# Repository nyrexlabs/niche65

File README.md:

# niche65

The niche65 is an open source proof of concept for a split, staggered, true-wireless Bluetooth 65% mechanical keyboard. Powered by ZMK.

## No support

This project is no longer supported. All development efforts are going towards a V2.

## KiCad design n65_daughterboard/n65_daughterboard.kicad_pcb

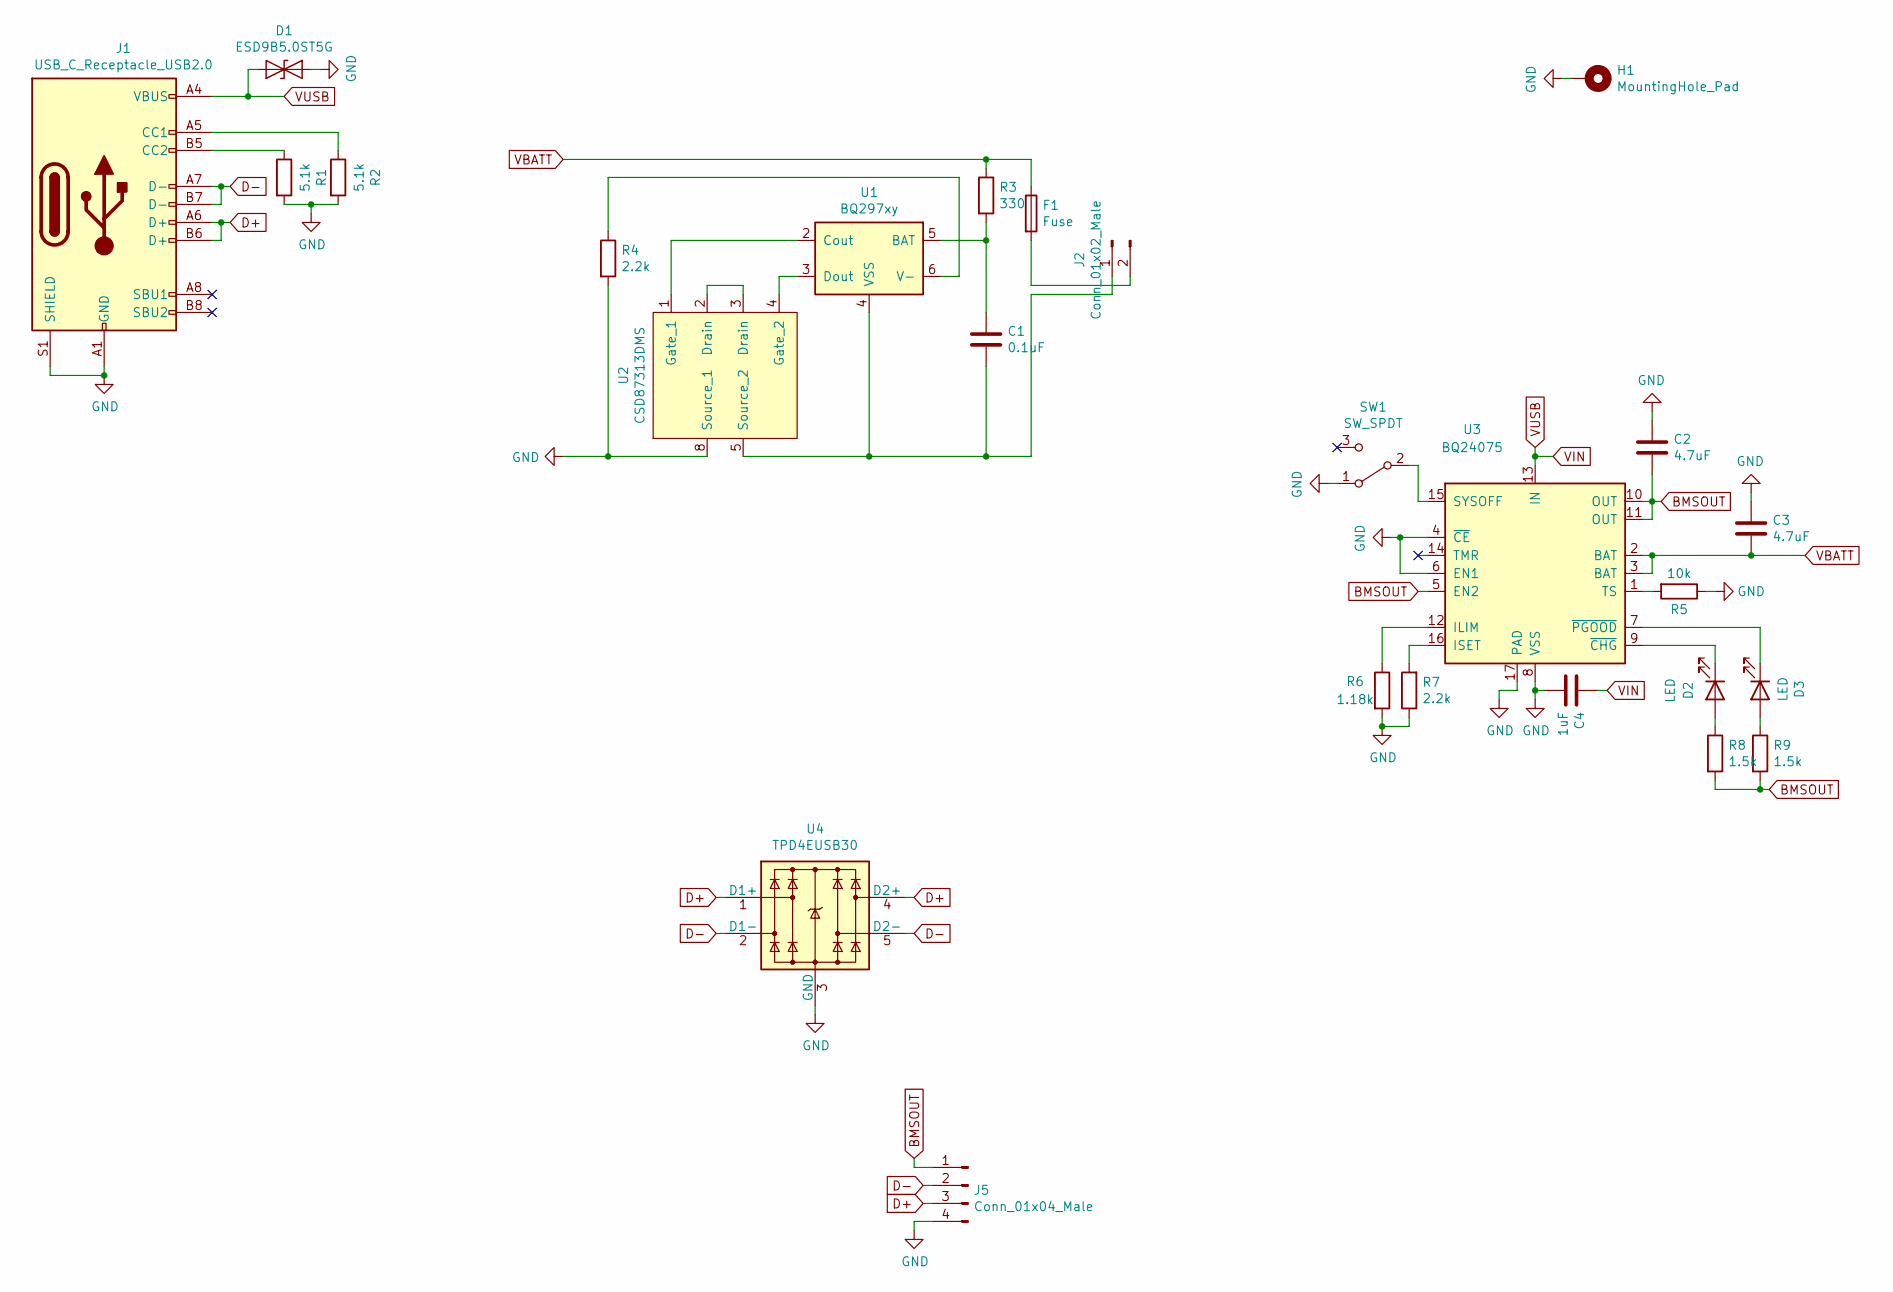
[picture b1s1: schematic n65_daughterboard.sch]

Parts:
C1: 0.1uF; C_0201_0603Metric
C2, C3: 4.7uF; C_0402_1005Metric
C4: 1uF; C_0201_0603Metric
D1: ESD9B5.0ST5G; D_0402_1005Metric
D2, D3: LED; LED_0603_1608Metric
F1: Fuse; Fuse_1206_3216Metric
H1: MountingHole_Pad; Screw Ground Pad 2mmID 5mmOD
J1: USB_C_Receptacle_USB2.0; GCT_USB4145_03_0170_C
J2: Conn_01x02_Male; JST_PH_S2B-PH-SM4-TB_1x02-1MP_P2.00mm_Horizontal
J5: Conn_01x04_Male; Molex_Pico-EZmate_78171-0004_1x04-1MP_P1.20mm_Vertical
R1, R2: 5.1k; R_0603_1608Metric
R3: 330; R_0603_1608Metric
R4, R7: 2.2k; R_0603_1608Metric
R5: 10k; R_0603_1608Metric
R6: 1.18k; R_0603_1608Metric
R8, R9: 1.5k; R_0603_1608Metric
SW1: SW_SPDT; SW_SPDTx01_Toggle_8.13x5.08mm_W7.62mm_P2.54mm
U1: BQ297xy; WSON-6_1.5x1.5mm_P0.5mm
U2: CSD87313DMS; VSON-8_3.3x3.3mm_P0.65mm_NexFET_NOTSTUPID
U3: BQ24075; VQFN-16-1EP_3x3mm_P0.5mm_EP1.68x1.68mm_ThermalVias
U4: TPD4EUSB30; USON-10_2.5x1.0mm_P0.5mm

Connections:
BMSOUT: C2.2, J5.1, R8.2, R9.2, U3.5 (EN2), U3.10 (OUT), U3.11 (OUT)
D+: J1.A6 (D+), J1.B6 (D+), J5.3, U4.1 (D1+), U4.4 (D2+)
D-: J1.A7 (D-), J1.B7 (D-), J5.2, U4.2 (D1-), U4.5 (D2-)
GND: C2.1, C3.1, C4.2, D1.2 (A2), H1.1, J1.A1 (GND), J1.A12 (GND), J1.B1 (GND), J1.B12 (GND), J1.S1 (SHIELD), J5.4, R1.2, R2.2, R4.2, R5.1, R6.2, R7.1, SW1.1 (A), U2.8 (Source_1), U3.4 (~CE), U3.6 (EN1), U3.8 (VSS), U3.17 (PAD), U4.3 (GND), U4.8 (GND); also elsewhere on the board
unnamed: C1.1, R3.2, U1.5 (BAT)
unnamed: C1.2, J2.1, U1.4 (VSS), U2.5 (Source_2)
unnamed: D2.1 (K), U3.9 (~CHG)
unnamed: D2.2 (A), R8.1
unnamed: D3.1 (K), U3.7 (~PGOOD)
unnamed: D3.2 (A), R9.1
unnamed: F1.2, J2.2
unnamed: J1.A5 (CC1), R2.1
unnamed: J1.B5 (CC2), R1.1
unnamed: R4.1, U1.6 (V-)
unnamed: R5.2, U3.1 (TS)
unnamed: R6.1, U3.12 (ILIM)
unnamed: R7.2, U3.16 (ISET)
unnamed: SW1.2 (B), U3.15 (SYSOFF)
unnamed: U1.2 (Cout), U2.1 (Gate_1)
unnamed: U1.3 (Dout), U2.4 (Gate_2)
unnamed: U2.2 (Drain), U2.3 (Drain)
VBATT: C3.2, F1.1, R3.1, U3.2 (BAT), U3.3 (BAT)
VIN: C4.1, D1.1 (A1), J1.A4 (VBUS), J1.A9 (VBUS), J1.B4 (VBUS), J1.B9 (VBUS), U3.13 (IN)

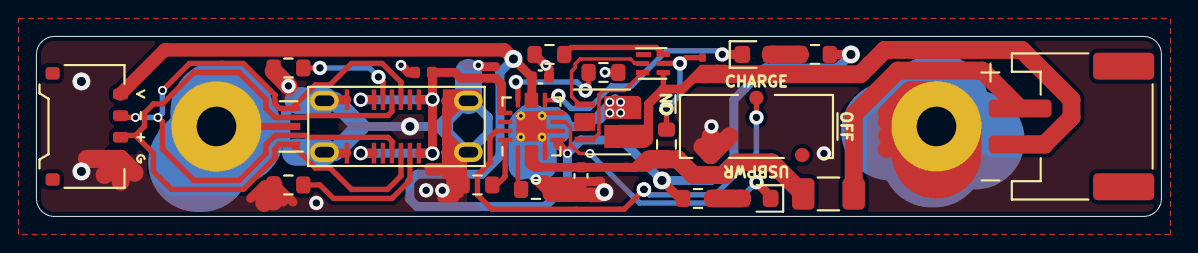
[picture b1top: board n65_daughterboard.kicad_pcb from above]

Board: 2 copper layers, 62.5 x 10.0 mm, 27 parts (0 on the bottom side), 23 nets.

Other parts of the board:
H1#2: MountingHole_Pad; Screw Ground Pad 2mmID 5mmOD

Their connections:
GND: H1#2.1; also elsewhere on the board

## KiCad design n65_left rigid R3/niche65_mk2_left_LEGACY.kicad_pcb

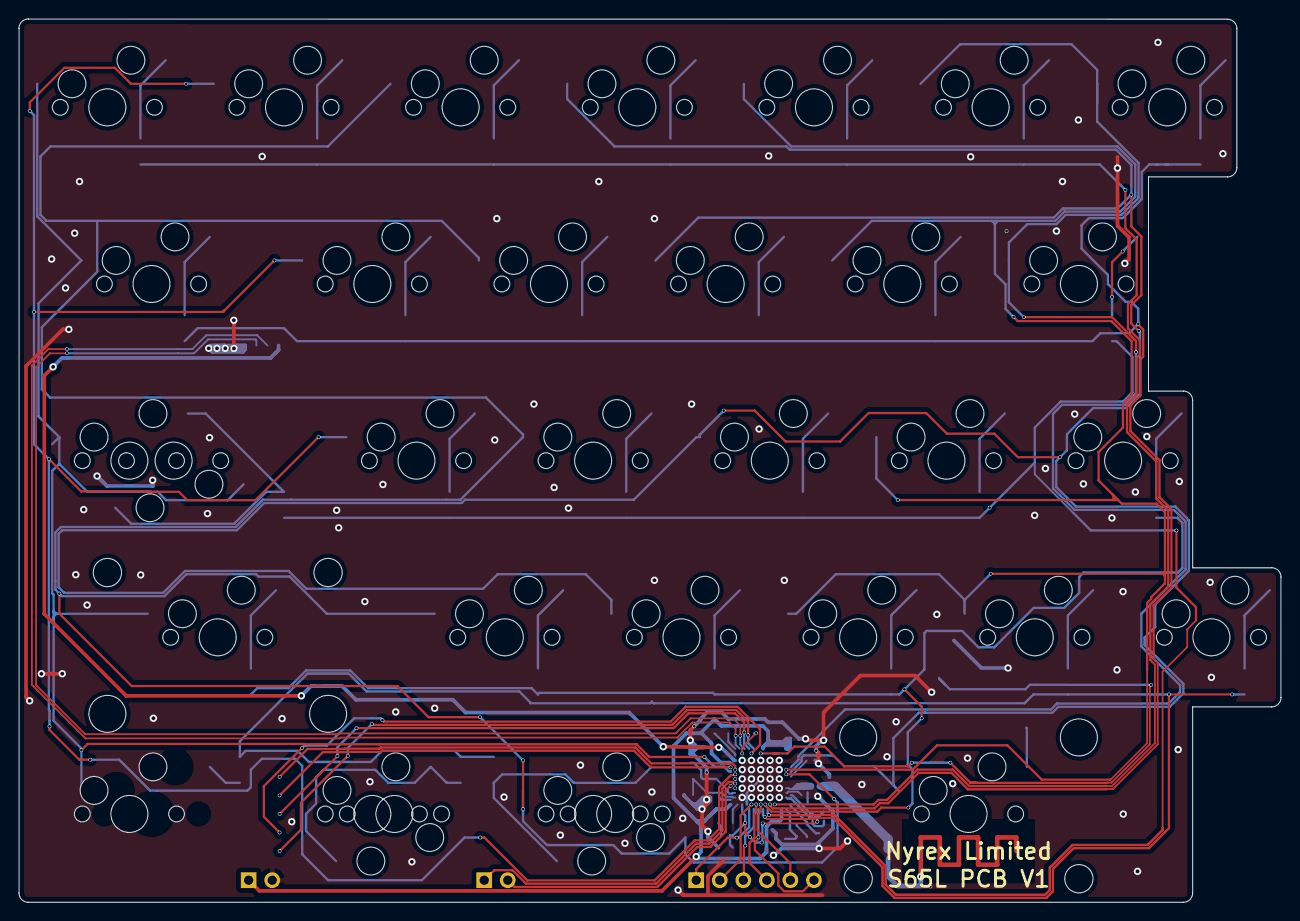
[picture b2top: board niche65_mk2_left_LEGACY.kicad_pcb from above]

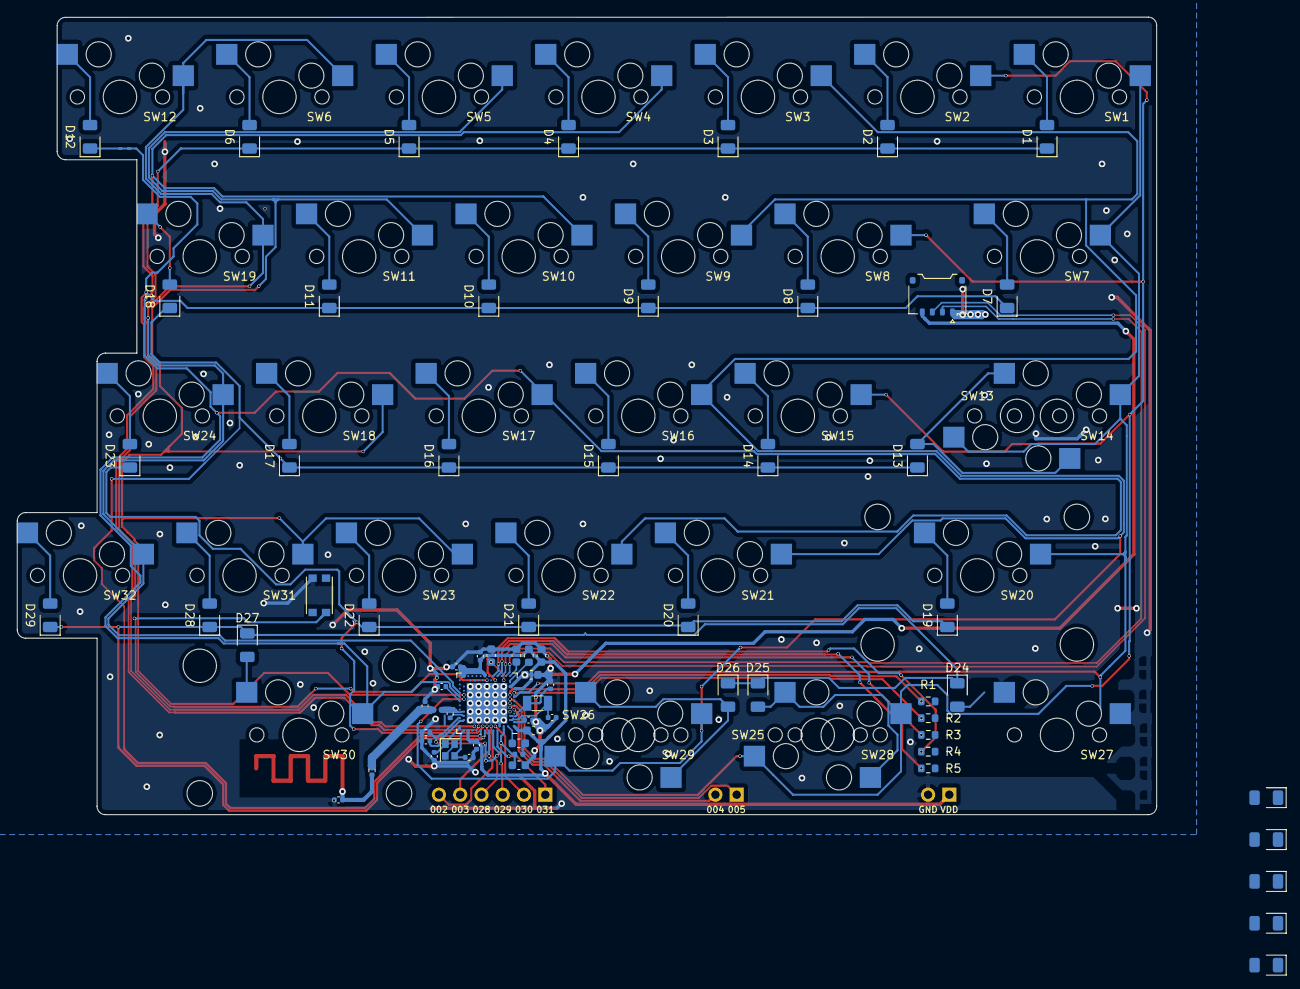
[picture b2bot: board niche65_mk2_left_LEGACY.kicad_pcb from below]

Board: 2 copper layers, 136.1 x 95.2 mm, 104 parts (72 on the bottom side), 80 nets.

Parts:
C1, C6, C7, C10: 4.7uF; C_0603_1608Metric
C2, C3, C4, C13: 100nF; C_0402_1005Metric
C5, C8: 1uF; C_0603_1608Metric
C9: 47nF; C_0402_1005Metric
C11: 820pF; C_0402_1005Metric
C12: 100pF; C_0402_1005Metric
C14, C15, C19, C20: 12pF; C_0402_1005Metric
C16: 1.5pF; C_0402_1005Metric
C17, C18: 1pF; C_0402_1005Metric
D1, D2, D3, D4, D5, D6, D7, D8, D9, D10, D11, D12, D13, D14, D15, D16, D17, D18, D19, D20, D21, D22, D23, D24, D25, D26, D27, D28, D29: D; D_1206_3216Metric
D30, D31, D32, D33, D34: LED; LED_1206_3216Metric
J1: Conn_01x04_Male; Molex_Pico-EZmate_78171-0004_1x04-1MP_P1.20mm_Vertical
J2: Conn_01x06_Female; PinHeader_1x06_P2.54mm_Vertical
J3, J4: Conn_01x02_Female; PinHeader_1x02_P2.54mm_Vertical
L1: 15nH; L_0402_1005Metric
L2, L3: 10uH; L_0603_1608Metric
L4: 4.7nH; L_0402_1005Metric
R1, R2, R3, R4, R5: 750; R_0603_1608Metric
R6: 50; R_0402_1005Metric
SW1, SW2, SW3, SW4, SW5, SW6, SW7, SW8, SW9, SW10, SW11, SW12, SW13, SW14, SW15, SW16, SW17, SW18, SW19, SW20, SW21, SW22, SW23, SW24, SW25, SW26, SW27, SW28, SW29, SW30, SW31, SW32: SW_Push; Kailh_socket_MX
SW33: SW_Push; SW_Push_1P1T_NO_CK_KMR2
U1: nRF52840; Nordic_AQFN-73-1EP_7x7mm_P0.5mm
Y1: 32.768kHz; Crystal_SMD_3215-2Pin_3.2x1.5mm
Y2: 32MHz; Crystal_SMD_2016-4Pin_2.0x1.6mm

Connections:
002: J2.6, U1.A12
003: J2.5, U1.B13
004: J3.2, U1.J1
005: J3.1, U1.K2
011: R1.2, U1.T2
012: R2.2, U1.U1
013: R3.2, U1.AD8
014: R4.2, U1.AC9
015: R5.2, U1.AD10
028: J2.4, U1.B11
029: J2.3, U1.A10
030: J2.2, U1.B9
031: J2.1, U1.A8
104: SW6.2, SW12.2, SW19.2, SW24.2, SW32.2, U1.U24
105: SW5.2, SW11.2, SW18.2, SW23.2, SW31.2, U1.T23
106: SW4.2, SW10.2, SW17.2, SW22.2, SW30.2, U1.R24
107: SW3.2, SW9.2, SW16.2, SW21.2, SW26.2, SW29.2, U1.P23
108: SW2.2, SW8.2, SW15.2, SW25.2, SW28.2, U1.P2
109: SW1.2, SW7.2, SW13.2, SW14.2, SW20.2, SW27.2, U1.R1
111: D1.1, D2.1, D3.1, D4.1, D5.1, D6.1, U1.B19
112: D7.1, D8.1, D9.1, D10.1, D11.1, D12.1, U1.B17
113: D13.1, D14.1, D15.1, D16.1, D17.1, D18.1, U1.A16
114: D19.1, D20.1, D21.1, D22.1, D23.1, U1.B15
115: D24.1, D25.1, D26.1, D27.1, D28.1, D29.1, U1.A14
Antenna: C16.1, R6.2
D+: J1.2, U1.AD6
D-: J1.3, U1.AD4
GND: C1.2, C2.2, C3.2, C4.2, C5.2, C6.2, C7.1, C8.1, C9.1, C10.2, C11.2, C12.2, C13.2, C14.1, C15.1, C16.2, C17.2, C18.2, C19.2, C20.2, D30.1, D31.1, D32.1, D33.1, D34.1, J1.1, J4.2, SW33.2, U1.B7, U1.EP, U1.F23, Y2.3, Y2.4
unnamed: C8.2, C9.2, L1.1, U1.B5, U1.E24
unnamed: C10.1, U1.AC5
unnamed: C11.1, U1.N24
unnamed: C12.1, U1.D23
unnamed: C13.1, U1.C1
unnamed: C14.2, U1.D2, Y1.1
unnamed: C15.2, U1.F2, Y1.2
unnamed: C17.1, L4.1, R6.1
unnamed: C18.1, L4.2, U1.H23
unnamed: C19.1, U1.B24, Y2.1
unnamed: C20.1, U1.A23, Y2.2
unnamed: D1.2, SW1.1
unnamed: D2.2, SW2.1
unnamed: D3.2, SW3.1
unnamed: D4.2, SW4.1
unnamed: D5.2, SW5.1
unnamed: D6.2, SW6.1
unnamed: D7.2, SW7.1
unnamed: D8.2, SW8.1
unnamed: D9.2, SW9.1
unnamed: D10.2, SW10.1
unnamed: D11.2, SW11.1
unnamed: D12.2, SW12.1
unnamed: D13.2, SW13.1, SW14.1
unnamed: D14.2, SW15.1
unnamed: D15.2, SW16.1
unnamed: D16.2, SW17.1
unnamed: D17.2, SW18.1
unnamed: D18.2, SW19.1
unnamed: D19.2, SW20.1
unnamed: D20.2, SW21.1
unnamed: D21.2, SW22.1
unnamed: D22.2, SW23.1
unnamed: D23.2, SW24.1
unnamed: D24.2, SW27.1
unnamed: D25.2, SW25.1, SW28.1
unnamed: D26.2, SW26.1, SW29.1
unnamed: D27.2, SW30.1
unnamed: D28.2, SW31.1
unnamed: D29.2, SW32.1
unnamed: D30.2, R1.1
unnamed: D31.2, R2.1
unnamed: D32.2, R3.1
unnamed: D33.2, R4.1
unnamed: D34.2, R5.1
unnamed: L1.2, L2.1
unnamed: L2.2, U1.B3
unnamed: L3.1, U1.AB2
RESET: SW33.1, U1.AC13
VBUS: C7.2, U1.AD2
VDDH: C6.1, J1.4, U1.Y2
VDD_NRF: C1.1, C2.1, C3.1, C4.1, C5.1, J4.1, L3.2, U1.A22, U1.AD14, U1.AD23, U1.B1, U1.W1

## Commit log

2024-03-11 Add KiCad PCB files (L/R/DB)
